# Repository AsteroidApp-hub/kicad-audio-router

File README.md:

# kicad-audio-router

An autorouter for KiCad that routes audio boards the way an audio designer would.
**Status: early (0.1.0).** [日本語](README.ja.md) · [Changelog](CHANGELOG.md)

General-purpose autorouters connect everything but know nothing about audio: they run analog signals
next to clocks, split balanced pairs, and leave ground pads far from a via. kicad-audio-router (`kar`)
reads your board, works out which nets are analog, digital, power and ground, and routes it with that in mind:

- analog tracks keep away from digital copper, more so from clocks than from relay drivers
- the two sides of a balanced pair run side by side
- every SMD ground pad gets its own via to the ground plane before any signal is routed
- power tracks get their full width, narrowed only where a fine-pitch pin forces it
- clearances are checked against the real copper shapes, with your net classes, hole clearance and
  keep-out areas, so the result passes KiCad's DRC

It is pure Python on top of KiCad's own `pcbnew` module: no Java, no other packages. The same board gives
the same result (unless a time limit cuts a step short on a very busy machine), and every command can report
in JSON for scripts and AI-driven flows.

*The demo board (`examples/`): a balanced line receiver next to a 74HC595 LED driver whose control lines
have to get past the analog path. Routed in about 4 s. Red: analog, blue: digital, orange: power.*

## Results

Seven real audio boards (a monitor controller, mic preamps, phantom supplies, a VU meter and a tape
saturator) were stripped of all tracks and routed from scratch with `kar auto`, each with its own design
rules and net classes, then compared with their original routing (by hand or with Freerouting).
The score is from `kar report` (0–100, higher is better; see [What the report measures](#what-the-report-measures)).

| board | layers | original | kar | time |
|---|---|---|---|---|
| monitor controller (~270 parts, relays, MUSES72320) | 4 | 52.4 | 85.9 | 143 s |
| VU meter (USB-C) | 2 | 75.7 | 94.1 | 24 s |
| tape saturator | 4 | 81.1 | 91.0 | 59 s |
| P48 phantom supply | 4 | 82.5 | 83.2 | 23 s |
| 2-ch mic preamp (discrete) | 4 | 79.6 | 81.7 | 28 s |
| mic preamp (op-amp) | 2 | 78.0 | 85.1 | 81 s |
| phantom power unit | 2 | 99.3 | 100.0 | 8 s |

Eight more boards by other designers, taken from public GitHub projects and routed the same way
(tested locally only; the boards are not part of this repository):

| board | layers | original | kar | time |
|---|---|---|---|---|
| PCM1792A DAC (I2S in, analog out) | 2 | 55.0 | 86.7 | 40 s |
| 4-channel eurorack mixer | 2 | 63.1 | 93.5 | 7 s |
| NE5532 preamp (unrouted original) | 2 | 45.0 | 99.4 | 8 s |
| THAT1512 microphone | 2 | 89.1 | 99.1 | 9 s |
| power amplifier preamp | 2 | 90.0 | 99.8 | 8 s |
| NE5532 headphone amplifier | 2 | 98.4 | 100.0 | 9 s |
| tone control | 2 | 99.7 | 100.0 | 5 s |
| RIAA phono preamp | 2 | 100.0 | 100.0 | 6 s |

All fifteen boards were fully routed. kar introduced no DRC problems, at any severity; the only ones left
(overlapping courtyards and footprints, pads of one footprint too close together, an open board outline)
were already in the original boards, and kar's routing has fewer of them than the originals.

## Installation

kar runs in the Python that comes with KiCad, because that is where `pcbnew` lives.

```sh
# the Python that comes with KiCad
#   macOS:   KPY=/Applications/KiCad/KiCad.app/Contents/Frameworks/Python.framework/Versions/Current/bin/python3
#   Windows: KPY="C:\Program Files\KiCad\9.0\bin\python.exe"
#   Linux:   KPY=python3            (the system Python that KiCad's pcbnew module is installed for)

$KPY -m pip install git+https://github.com/AsteroidApp-hub/kicad-audio-router
$KPY -m kar doctor --demo           # checks your KiCad and routes the demo board; every line should say ok
```

Without pip, clone the repository and run `$KPY -m kar ...` from its folder.

To get a button in KiCad's PCB editor toolbar, run `$KPY -m kar plugin install` and restart KiCad. The button
saves the board, routes a copy and writes it next to it as `<board>_kar.kicad_pcb` (the open board is not
changed), then shows the score and the DRC result. `$KPY -m kar plugin remove` takes it out again.

## Quick start

1. Place the parts in KiCad and save. kar does not move footprints; the placement decides a lot.
2. Route, check and report in one go:

   ```sh
   $KPY -m kar auto board.kicad_pcb -o routed/board.kicad_pcb
   ```

   This writes `routed/board.kicad_pcb` (with the project file, so your rules travel with it) and, in
   `routed/kar_out/`, the DRC result, the quality report and the route log.
3. Open the routed board in KiCad, look at it, run the DRC. Always do this before ordering.

## Working with the result

### Reviewing

- Everything kar places goes into PCB groups named `kar: analog`, `kar: digital`, `kar: power`,
  `kar: ground` and `kar: other`. Click a group in KiCad to select that kind of copper at once.
- The route log (`*_route.md` / `.json`) lists each net's length, vias, widths and layers, and every
  step that needed more than a plain route: pins reached on a finer grid, nets that pushed others aside
  (and which ones they moved), power nets narrowed below their width.
- The quality report (`*_quality.md` / `.json`) gives board coordinates (x, y, layer) for the places to look
  at: where each analog net comes closest to digital copper, and where power tracks are narrower than
  their net class width.
- `kar plot routed/board.kicad_pcb -o board.svg` draws the routing per layer, coloured by net class.

### Fixing things by hand, then re-routing

1. Change what you do not like in KiCad: move or redraw tracks, delete them, route a few nets yourself.
2. To keep a track kar placed exactly as it is, take it out of its `kar: ...` group (Remove from group).
   Tracks you draw yourself are not in a group anyway.
3. Run again with `--rip-kar`:

   ```sh
   $KPY -m kar auto board_edited.kicad_pcb -o routed_v2/board.kicad_pcb --rip-kar
   $KPY -m kar route board_edited.kicad_pcb -o board_v2.kicad_pcb --rip-kar --nets /SCLK,/SDATA   # only these
   ```

   kar removes the copper still in its groups, leaves everything else exactly where it is (it does not
   push it aside), and routes the rest. Nets that you routed part of are completed from that copper.

## Commands

| command | what it does |
|---|---|
| `auto` | `route` → `ground` → KiCad DRC (kicad-cli) → `report`, with a JSON summary |
| `route` | routes the nets (`--classes analog,power,digital,other`, `--nets`, `--rip-kar`, `--log DIR`) |
| `ground` | a via for every ground pad far from one, repair of pour islands, optional pours (`--pour F.Cu,B.Cu`) |
| `report` | routing quality report and score |
| `classify` | how each net was classified, and why |
| `plot` | SVG picture of the routing, one panel per layer, coloured by net class |
| `doctor` | checks that your KiCad offers what kar needs (`--demo` also routes the demo board) |
| `bench DIR` | re-routes every board in a folder from scratch and compares with its original routing |
| `strip` | removes tracks and vias (`--kar-only`: only kar's) |
| `finish` | optional: hands nets kar could not route to Freerouting (DSN/SES); not needed on the test boards |

Run `$KPY -m kar <command> --help` for the options.

## How it routes

- A* search on a 0.25 mm grid over the routing layers, 8 directions plus vias. Inner layers whose type is
  *power* in the board setup are left to planes. The grid is aligned to fine-pitch pads.
- Clearance is checked exactly near copper: from a grid point, the distance to the real pad outline,
  track or via must leave the clearance of both net classes plus half the track width, with an
  allowance for the straight run to the next grid point.
- Costs: analog nets pay for running near digital copper, digital nets for running near analog copper,
  weighted by how often the digital net switches (clock, data, static). The second side of a balanced
  pair pays for leaving the line one track pitch beside the first; if the two still do not run together,
  a stronger pull and the reverse order are tried.
- Order: ground vias, pins that need a finer grid, balanced pairs, analog, power, digital, other.
- A net that does not fit is routed through other tracks at a price, and the tracks it crossed are routed
  again ("push"). What still fails is tried on a grid twice as fine around its pads.
- Power tracks narrowed in tight spots are widened afterwards where there is room; if a power net is
  still narrow, it is routed again at full width by pushing other tracks aside, and kept only if every
  pushed track finds a new way.

## What the report measures

| metric | meaning |
|---|---|
| coupling | analog copper within 1 mm and 3 mm (edge to edge, same layer) of digital copper, weighted by how active the digital net is (clock 1.0, data 0.6, static 0.15) |
| balanced pairs | length of each side, mismatch, and the share routed side by side away from the pins (pin positions decide the rest) |
| ground return | SMD pads of each ground net farther than 3 mm (from the pad edge) from a via or through-hole pad of the same net |
| power width | length of power track narrower than its net class width (0.4 mm without a class); neck-downs into fine-pitch pins are not counted |
| analog vias | vias on analog nets |
| unrouted | unconnected items reported by KiCad |

The score weights these for audio work so that two routings of the same board can be compared.
It is a comparison aid, not an absolute grade.

## How nets are classified

1. explicit patterns in the rules file
2. ground and power by name (`GND`, `AGND`, `CHASSIS`, `+15V`, `VCC`, …)
3. digital by name (`SCLK`, `SDA`, `LATCH`, …), by touching a digital IC (`74*`, `ULN*`, MCUs, …), or a
   digital pin of a mixed-signal IC
4. analog: pins of analog ICs (`OPA*`, `NE5532`, `NJM*`, `MUSES*`, …) and audio connectors (by footprint,
   value or reference: XLR, jack, `MIC IN`, `OUT L`, `JINL`), spread through resistors, capacitors,
   transistors, switches, transformers, pots, diodes and relay contacts
5. balanced pairs: names that differ by `_H`/`_C`, `_P`/`_N`, `+`/`-` or `HOT`/`COLD`, `POS`/`NEG`, and that
   connect to the same kinds of parts

House-style designators (`RGaR` for a resistor, `DBL` for a diode, `RLL` with value `HFD27` for a relay) are
recognised. Check the result with `kar classify` and override anything with a rules file
(`--rules rules.json`; see `examples/rules.example.json` and the top of `kar/rules.py`).

## Limitations

- kar routes on a grid (0.25 mm, 0.125 mm where needed). Very fine-pitch parts (BGAs, 0.4 mm QFNs) are
  out of reach for now.
- No length matching, impedance control or true coupled differential-pair routing: balanced pairs run
  side by side where the pins allow, which is what audio boards need.
- Tracks are straight segments at 45° steps; no arcs or teardrops.
- kar does not move parts or shape copper pours beyond ground vias and island repair.
- It is Python: a dense 4-layer board with ~270 parts takes a few minutes.
- Tested on KiCad 10 (macOS) and KiCad 9 (Linux, official Docker image). Windows is expected to work but
  has not been tried yet ([docs/compatibility.md](docs/compatibility.md)); please report what you find.

## Contributing

Bug reports with a board that shows the problem help most; see [CONTRIBUTING.md](CONTRIBUTING.md).

```sh
python3 tests/test_core.py        # pure-Python tests, no KiCad needed
$KPY tests/test_kicad.py          # demo board end to end, re-route after hand edits
$KPY -m kar bench path/to/boards  # re-route a folder of your boards and compare
```

## License

MIT

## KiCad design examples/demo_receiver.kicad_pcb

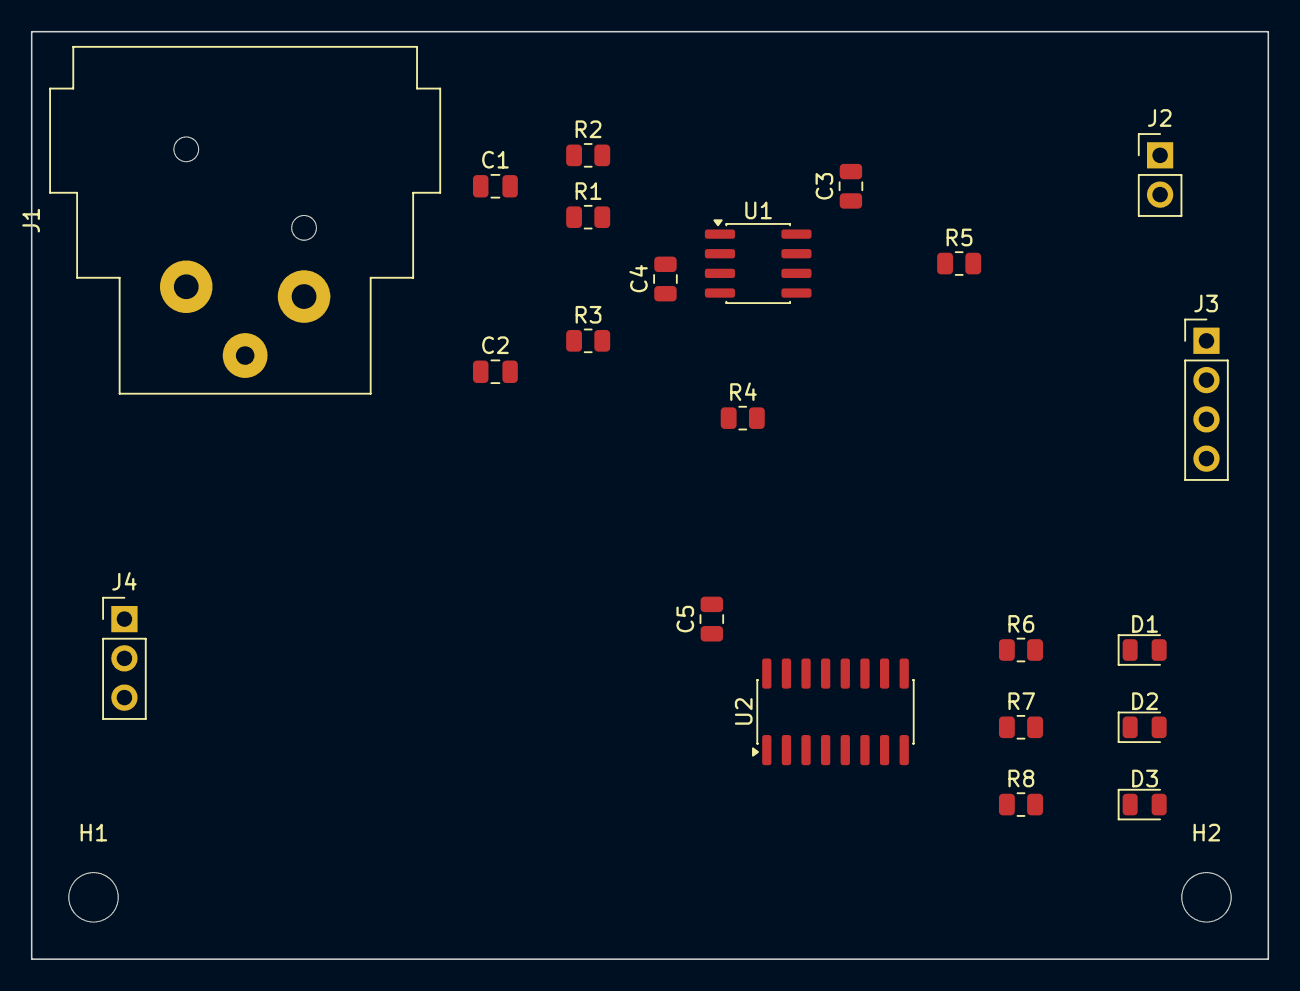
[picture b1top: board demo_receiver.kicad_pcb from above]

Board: 4 copper layers, 80.0 x 60.0 mm, 24 parts (0 on the bottom side), 20 nets, no tracks yet.

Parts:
C1, C2: 470p; C_0805_2012Metric
C3, C4, C5: 100n; C_0805_2012Metric
D1, D2, D3: LED; LED_0805_2012Metric
H1, H2: MountingHole_3.2mm_M3
J1: XLR IN; Jack_XLR_Neutrik_NC3FAAH_Horizontal
J2: OUT; PinHeader_1x02_P2.54mm_Vertical
J3: PWR; PinHeader_1x04_P2.54mm_Vertical
J4: CTRL; PinHeader_1x03_P2.54mm_Vertical
R1, R2, R3, R4: 10k; R_0805_2012Metric
R5: 47; R_0805_2012Metric
R6, R7, R8: 1k; R_0805_2012Metric
U1: OPA1612; SOIC-8_3.9x4.9mm_P1.27mm
U2: 74HC595; SOIC-16_3.9x9.9mm_P1.27mm

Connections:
/+5V: C5.1, J3.4, U2.10, U2.16
/+15V: C3.1, J3.1, U1.8
/-15V: C4.2, J3.3, U1.4
/BUF: R5.1, U1.6, U1.7
/IN_C: C2.1, J1.3, R3.1
/IN_H: C1.1, J1.2, R1.1
/LA: D1.2, R6.2
/LATCH: J4.3, U2.12
/LB: D2.2, R7.2
/LC: D3.2, R8.2
/OUT: J2.1, R5.2
/QA: R6.1, U2.15
/QB: R7.1, U2.1
/QC: R8.1, U2.2
/RX_N: R3.2, R4.1, U1.2
/RX_OUT: R4.2, U1.1, U1.5
/RX_P: R1.2, R2.1, U1.3
/SCLK: J4.1, U2.11
/SDATA: J4.2, U2.14
GND: C1.2, C2.2, C3.2, C4.1, C5.2, D1.1, D2.1, D3.1, J1.1, J2.2, J3.2, R2.2, U2.8, U2.13
